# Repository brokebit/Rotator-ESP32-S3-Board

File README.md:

# Rotator-ESP32-S3-Board

# Features / Design Info
- One of the ESP32 serial ports exposes a GS-232 interface for motor control commands for connecting to a PC interfacing with rotctld from the Hamlib suite
- GPS Time Sync using NEMA GPS Module over RS232
- Serial interface for Nextion Display
- Designed for Clearpath servo motors from https://teknic.com/
- Interface for 6 Hardware Debounced buttons for manual direction control, homing and moon tracking 
- Uses pulse encoder data from the Clearpath motors for position feedback
- Power input is +10v - +25v DC
- Motors are powered by seperate power source 
- Voltage select headers to select either 3.3v or 5v logic for RS232 interfaces (GPS, LCD)
- 6 Layer Board

# Build Pics

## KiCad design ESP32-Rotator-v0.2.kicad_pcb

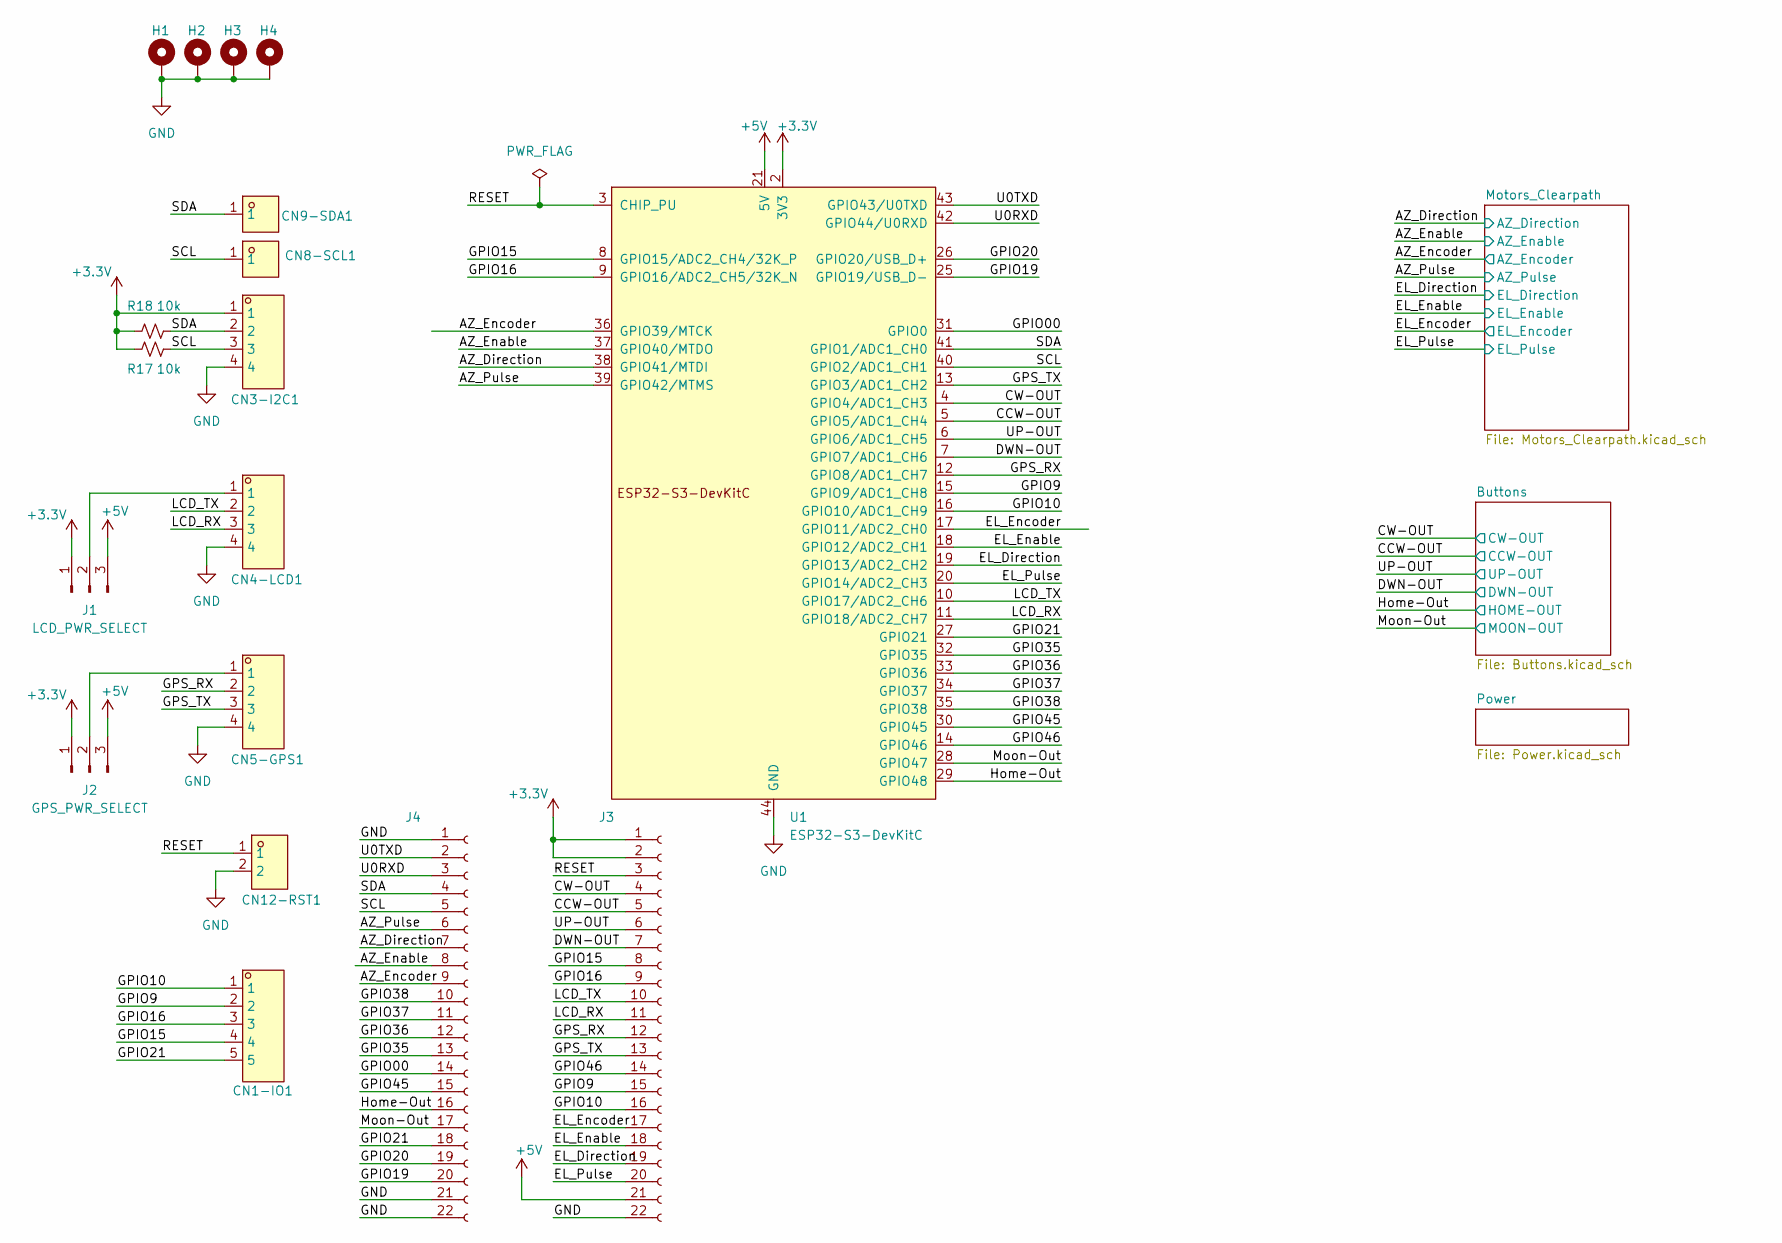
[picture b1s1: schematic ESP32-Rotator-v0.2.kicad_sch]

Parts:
CN1-IO1: WJ15EDGVC-3.81-5P; CONN-TH_WJ15EDGVC-3.81-5P; LCSC Part C8391
CN3-I2C1, CN4-LCD1, CN5-GPS1: WJ15EDGVC-3.81-4P; CONN-TH_4P-P3.81_WJ2EDGVC-3.81-4P; LCSC Part C8410
CN8-SCL1, CN9-SDA1: RH-5019; TESTPOINT-SMD_L3.8-W2.0_RH-5019; LCSC Part C5199800
CN12-RST1: KF2EDGV-3.81-2P; CONN-TH_2P-P3.81_KF2EDGV-3.81-2P; LCSC Part C441332
H1, H2, H3, H4: MountingHole_Pad; MountingHole_3.2mm_M3_Pad
J1: LCD_PWR_SELECT; PinHeader_1x03_P2.54mm_Vertical
J2: GPS_PWR_SELECT; PinHeader_1x03_P2.54mm_Vertical
J3, J4: Conn_01x22_Socket; PinSocket_1x22_P2.54mm_Vertical
R17, R18: 10k; R_0805_2012Metric
U1: ESP32-S3-DevKitC

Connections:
+3.3V: CN3-I2C1.1, J1.1, J2.1, J3.1, J3.2, R17.1, R18.1, U1.1 (3V3), U1.2 (3V3); also elsewhere on the board
+5V: J1.3, J2.3, J3.21, U1.21 (5V); also elsewhere on the board
/AZ_Direction: J4.7, U1.38 (GPIO41/MTDI); also elsewhere on the board
/AZ_Enable: J4.8, U1.37 (GPIO40/MTDO); also elsewhere on the board
/AZ_Encoder: J4.9, U1.36 (GPIO39/MTCK); also elsewhere on the board
/AZ_Pulse: J4.6, U1.39 (GPIO42/MTMS); also elsewhere on the board
/CCW-OUT: J3.5, U1.5 (GPIO5/ADC1_CH4); also elsewhere on the board
/CW-OUT: J3.4, U1.4 (GPIO4/ADC1_CH3); also elsewhere on the board
/DWN-OUT: J3.7, U1.7 (GPIO7/ADC1_CH6); also elsewhere on the board
/EL_Direction: J3.19, U1.19 (GPIO13/ADC2_CH2); also elsewhere on the board
/EL_Enable: J3.18, U1.18 (GPIO12/ADC2_CH1); also elsewhere on the board
/EL_Encoder: J3.17, U1.17 (GPIO11/ADC2_CH0); also elsewhere on the board
/EL_Pulse: J3.20, U1.20 (GPIO14/ADC2_CH3); also elsewhere on the board
/GPIO00: J4.14, U1.31 (GPIO0)
/GPIO9: CN1-IO1.2, J3.15, U1.15 (GPIO9/ADC1_CH8)
/GPIO10: CN1-IO1.1, J3.16, U1.16 (GPIO10/ADC1_CH9)
/GPIO15: CN1-IO1.4, J3.8, U1.8 (GPIO15/ADC2_CH4/32K_P)
/GPIO16: CN1-IO1.3, J3.9, U1.9 (GPIO16/ADC2_CH5/32K_N)
/GPIO19: J4.20, U1.25 (GPIO19/USB_D-)
/GPIO20: J4.19, U1.26 (GPIO20/USB_D+)
/GPIO21: CN1-IO1.5, J4.18, U1.27 (GPIO21)
/GPIO35: J4.13, U1.32 (GPIO35)
/GPIO36: J4.12, U1.33 (GPIO36)
/GPIO37: J4.11, U1.34 (GPIO37)
/GPIO38: J4.10, U1.35 (GPIO38)
/GPIO45: J4.15, U1.30 (GPIO45)
/GPIO46: J3.14, U1.14 (GPIO46)
/GPS_RX: CN5-GPS1.2, J3.12, U1.12 (GPIO8/ADC1_CH7)
/GPS_TX: CN5-GPS1.3, J3.13, U1.13 (GPIO3/ADC1_CH2)
/Home-Out: J4.16, U1.29 (GPIO48); also elsewhere on the board
/LCD_RX: CN4-LCD1.3, J3.11, U1.11 (GPIO18/ADC2_CH7)
/LCD_TX: CN4-LCD1.2, J3.10, U1.10 (GPIO17/ADC2_CH6)
/Moon-Out: J4.17, U1.28 (GPIO47); also elsewhere on the board
/RESET: CN12-RST1.1, J3.3, U1.3 (CHIP_PU)
/SCL: CN3-I2C1.3, CN8-SCL1.1, J4.5, R17.2, U1.40 (GPIO2/ADC1_CH1)
/SDA: CN3-I2C1.2, CN9-SDA1.1, J4.4, R18.2, U1.41 (GPIO1/ADC1_CH0)
/U0RXD: J4.3, U1.42 (GPIO44/U0RXD)
/U0TXD: J4.2, U1.43 (GPIO43/U0TXD)
/UP-OUT: J3.6, U1.6 (GPIO6/ADC1_CH5); also elsewhere on the board
GND: CN3-I2C1.4, CN4-LCD1.4, CN5-GPS1.4, CN12-RST1.2, H1.1, H2.1, H3.1, H4.1, J3.22, J4.1, J4.21, J4.22, U1.22 (GND), U1.23 (GND), U1.24 (GND), U1.44 (GND); also elsewhere on the board
unnamed: CN4-LCD1.1, J1.2
unnamed: CN5-GPS1.1, J2.2

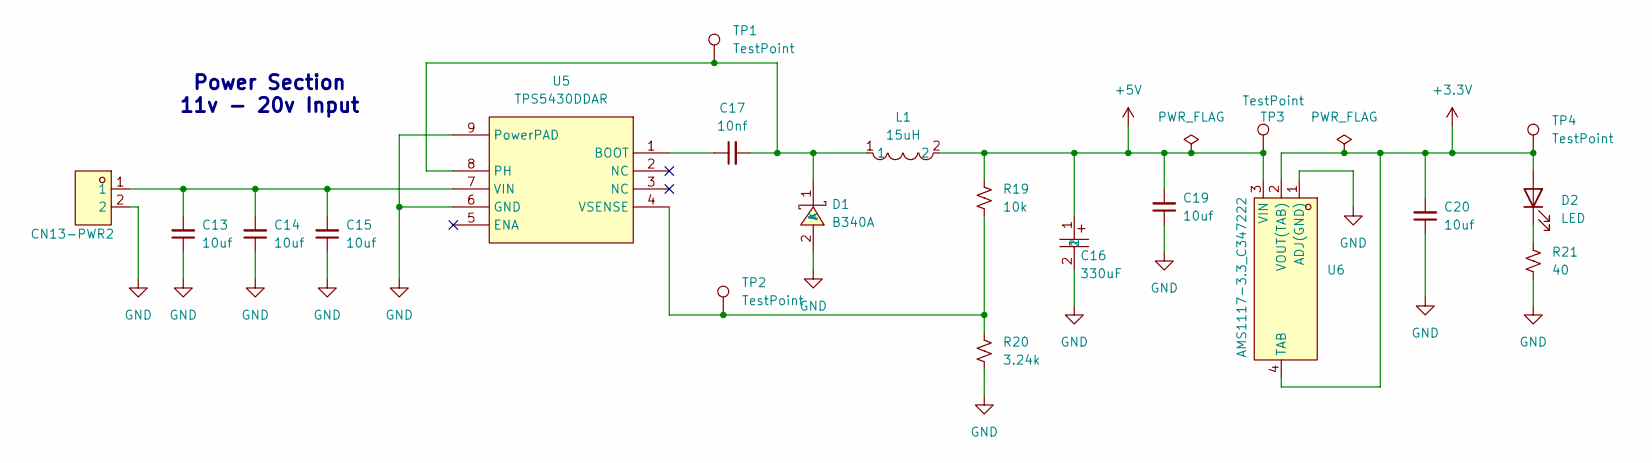
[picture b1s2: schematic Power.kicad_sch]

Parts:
C13, C14, C15, C19, C20: 10uf; C_0603_1608Metric
C16: 330uF; CAP-SMD_L7.3-W4.3-R-RD; LCSC Part C79112
C17: 10nf; C_0603_1608Metric
CN13-PWR2: KF2EDGV-3.81-2P; CONN-TH_2P-P3.81_KF2EDGV-3.81-2P; LCSC Part C441332
D1: B340A; SMA_L4.3-W2.6-LS5.1-RD; LCSC Part C64982
D2: LED; LED_0805_2012Metric; LCSC Part C84260
L1: 15uH; IND-SMD_L12.5-W12.5_RLF12545T; LCSC Part C40000
R19: 10k; R_0603_1608Metric
R20: 3.24k; R_0603_1608Metric
R21: 40; R_0805_2012Metric; LCSC Part C2930194
TP1, TP2, TP3, TP4: TestPoint; TestPoint_Pad_1.5x1.5mm
U5: TPS5430DDAR; ESOP-8_L4.9-W3.9-P1.27-LS6.0-TL-EP; LCSC Part C9864
U6: AMS1117-3.3_C347222; SOT-223-4_L6.5-W3.5-P2.30-LS7.0-BR; LCSC Part C347222

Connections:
+3.3V: C20.2, D2.2 (A), TP4.1, U6.2 (VOUT(TAB)), U6.4 (TAB); also elsewhere on the board
+5V: C16.1, C19.2, L1.2, R19.1, TP3.1, U6.3 (VIN); also elsewhere on the board
GND: C13.1, C14.1, C15.1, C16.2, C19.1, C20.1, CN13-PWR2.2, D1.2 (A), R20.2, R21.2, U5.6 (GND), U5.9 (PowerPAD), U6.1 (ADJ(GND)); also elsewhere on the board
unnamed: C17.2, D1.1 (K), L1.1, TP1.1, U5.8 (PH)
unnamed: D2.1 (K), R21.1
unnamed: C17.1, U5.1 (BOOT)
unnamed: C13.2, C14.2, C15.2, CN13-PWR2.1, U5.7 (VIN)
unnamed: R19.2, R20.1, TP2.1, U5.4 (VSENSE)

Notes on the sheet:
Power Section 11v - 20v Input

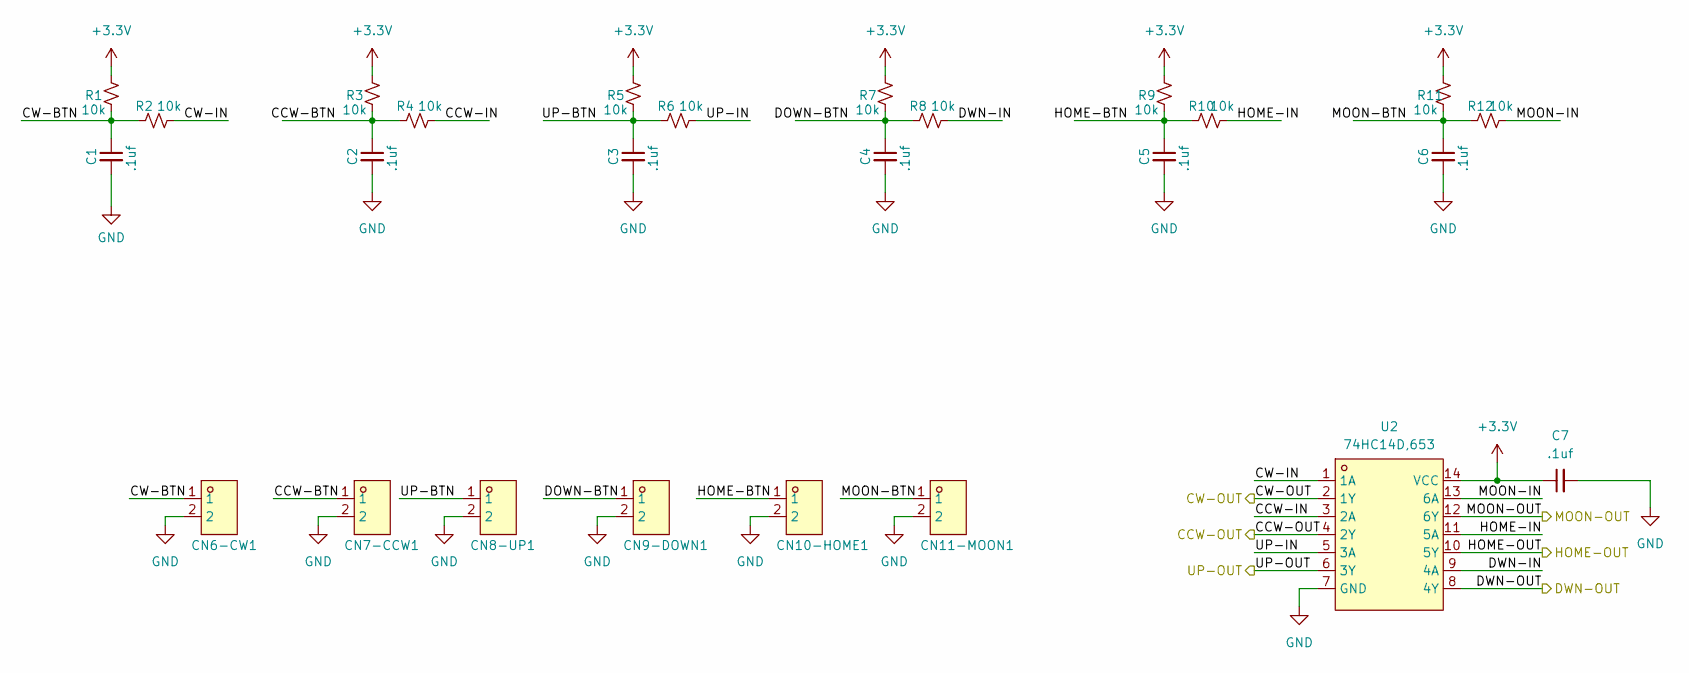
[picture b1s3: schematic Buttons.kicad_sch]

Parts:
C1, C2, C3, C4, C5, C6, C7: .1uf; C_0805_2012Metric
CN6-CW1, CN7-CCW1, CN8-UP1, CN9-DOWN1, CN10-HOME1, CN11-MOON1: KF2EDGV-3.81-2P; CONN-TH_2P-P3.81_KF2EDGV-3.81-2P; LCSC Part C441332
R1, R2, R3, R4, R5, R6, R7, R8, R9, R10, R11, R12: 10k; R_0805_2012Metric
U2: 74HC14D,653; SOIC-14_L8.7-W3.9-P1.27-LS6.0-BL; LCSC Part C5605

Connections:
+3.3V: C7.1, R1.1, R3.1, R5.1, R7.1, R9.1, R11.1, U2.14 (VCC); also elsewhere on the board
/Buttons/CCW-BTN: C2.1, CN7-CCW1.1, R3.2, R4.2
/Buttons/CCW-IN: R4.1, U2.3 (2A)
/Buttons/CW-BTN: C1.1, CN6-CW1.1, R1.2, R2.2
/Buttons/CW-IN: R2.1, U2.1 (1A)
/Buttons/DOWN-BTN: C4.1, CN9-DOWN1.1, R7.2, R8.2
/Buttons/DWN-IN: R8.1, U2.9 (4A)
/Buttons/HOME-BTN: C5.1, CN10-HOME1.1, R9.2, R10.2
/Buttons/HOME-IN: R10.1, U2.11 (5A)
/Buttons/MOON-BTN: C6.1, CN11-MOON1.1, R11.2, R12.2
/Buttons/MOON-IN: R12.1, U2.13 (6A)
/Buttons/UP-BTN: C3.1, CN8-UP1.1, R5.2, R6.2
/Buttons/UP-IN: R6.1, U2.5 (3A)
/CCW-OUT: U2.4 (2Y); also elsewhere on the board
/CW-OUT: U2.2 (1Y); also elsewhere on the board
/DWN-OUT: U2.8 (4Y); also elsewhere on the board
/Home-Out: U2.10 (5Y); also elsewhere on the board
/Moon-Out: U2.12 (6Y); also elsewhere on the board
/UP-OUT: U2.6 (3Y); also elsewhere on the board
GND: C1.2, C2.2, C3.2, C4.2, C5.2, C6.2, C7.2, CN6-CW1.2, CN7-CCW1.2, CN8-UP1.2, CN9-DOWN1.2, CN10-HOME1.2, CN11-MOON1.2, U2.7 (GND); also elsewhere on the board

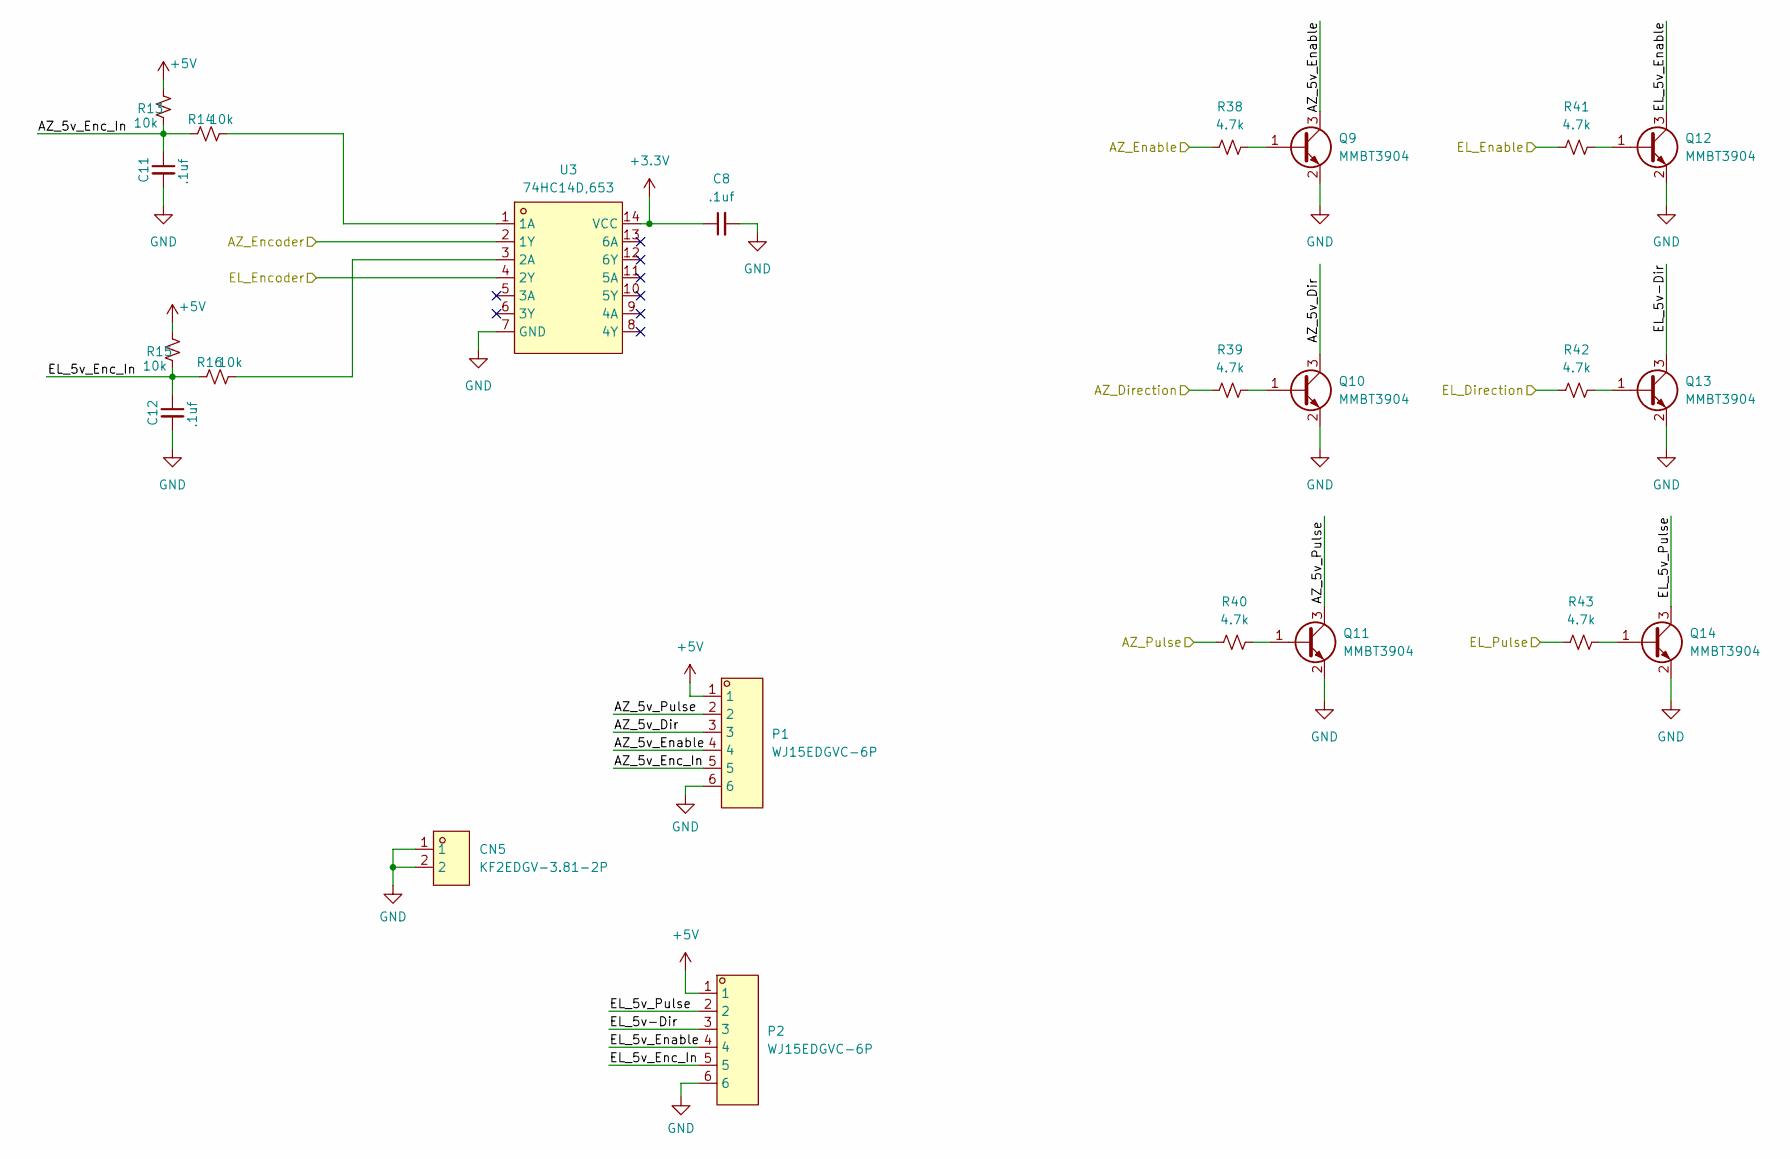
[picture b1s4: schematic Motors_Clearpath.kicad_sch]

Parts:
C8, C11, C12: .1uf; C_0805_2012Metric
CN5: KF2EDGV-3.81-2P; CONN-TH_2P-P3.81_KF2EDGV-3.81-2P; LCSC Part C441332
P1, P2: WJ15EDGVC-6P; CONN-TH_6P_WJ15EDGVC-3.81-6P; LCSC Part C8415
Q9, Q10, Q11, Q12, Q13, Q14: MMBT3904; SOT-23
R13, R14, R15, R16: 10k; R_0805_2012Metric
R38, R39, R40, R41, R42, R43: 4.7k; R_0805_2012Metric
U3: 74HC14D,653; SOIC-14_L8.7-W3.9-P1.27-LS6.0-BL; LCSC Part C5605

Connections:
+3.3V: C8.1, U3.14 (VCC); also elsewhere on the board
+5V: P1.1, P2.1, R13.1, R15.1; also elsewhere on the board
/AZ_Direction: R39.1; also elsewhere on the board
/AZ_Enable: R38.1; also elsewhere on the board
/AZ_Encoder: U3.2 (1Y); also elsewhere on the board
/AZ_Pulse: R40.1; also elsewhere on the board
/EL_Direction: R42.1; also elsewhere on the board
/EL_Enable: R41.1; also elsewhere on the board
/EL_Encoder: U3.4 (2Y); also elsewhere on the board
/EL_Pulse: R43.1; also elsewhere on the board
/Motors_Clearpath/AZ_5v_Dir: P1.3, Q10.3 (C)
/Motors_Clearpath/AZ_5v_Enable: P1.4, Q9.3 (C)
/Motors_Clearpath/AZ_5v_Enc_In: C11.1, P1.5, R13.2, R14.2
/Motors_Clearpath/AZ_5v_Pulse: P1.2, Q11.3 (C)
/Motors_Clearpath/EL_5v-Dir: P2.3, Q13.3 (C)
/Motors_Clearpath/EL_5v_Enable: P2.4, Q12.3 (C)
/Motors_Clearpath/EL_5v_Enc_In: C12.1, P2.5, R15.2, R16.2
/Motors_Clearpath/EL_5v_Pulse: P2.2, Q14.3 (C)
GND: C8.2, C11.2, C12.2, CN5.1, CN5.2, P1.6, P2.6, Q9.2 (E), Q10.2 (E), Q11.2 (E), Q12.2 (E), Q13.2 (E), Q14.2 (E), U3.7 (GND); also elsewhere on the board
unnamed: Q9.1 (B), R38.2
unnamed: Q10.1 (B), R39.2
unnamed: Q11.1 (B), R40.2
unnamed: Q12.1 (B), R41.2
unnamed: Q13.1 (B), R42.2
unnamed: Q14.1 (B), R43.2
unnamed: R14.1, U3.1 (1A)
unnamed: R16.1, U3.3 (2A)

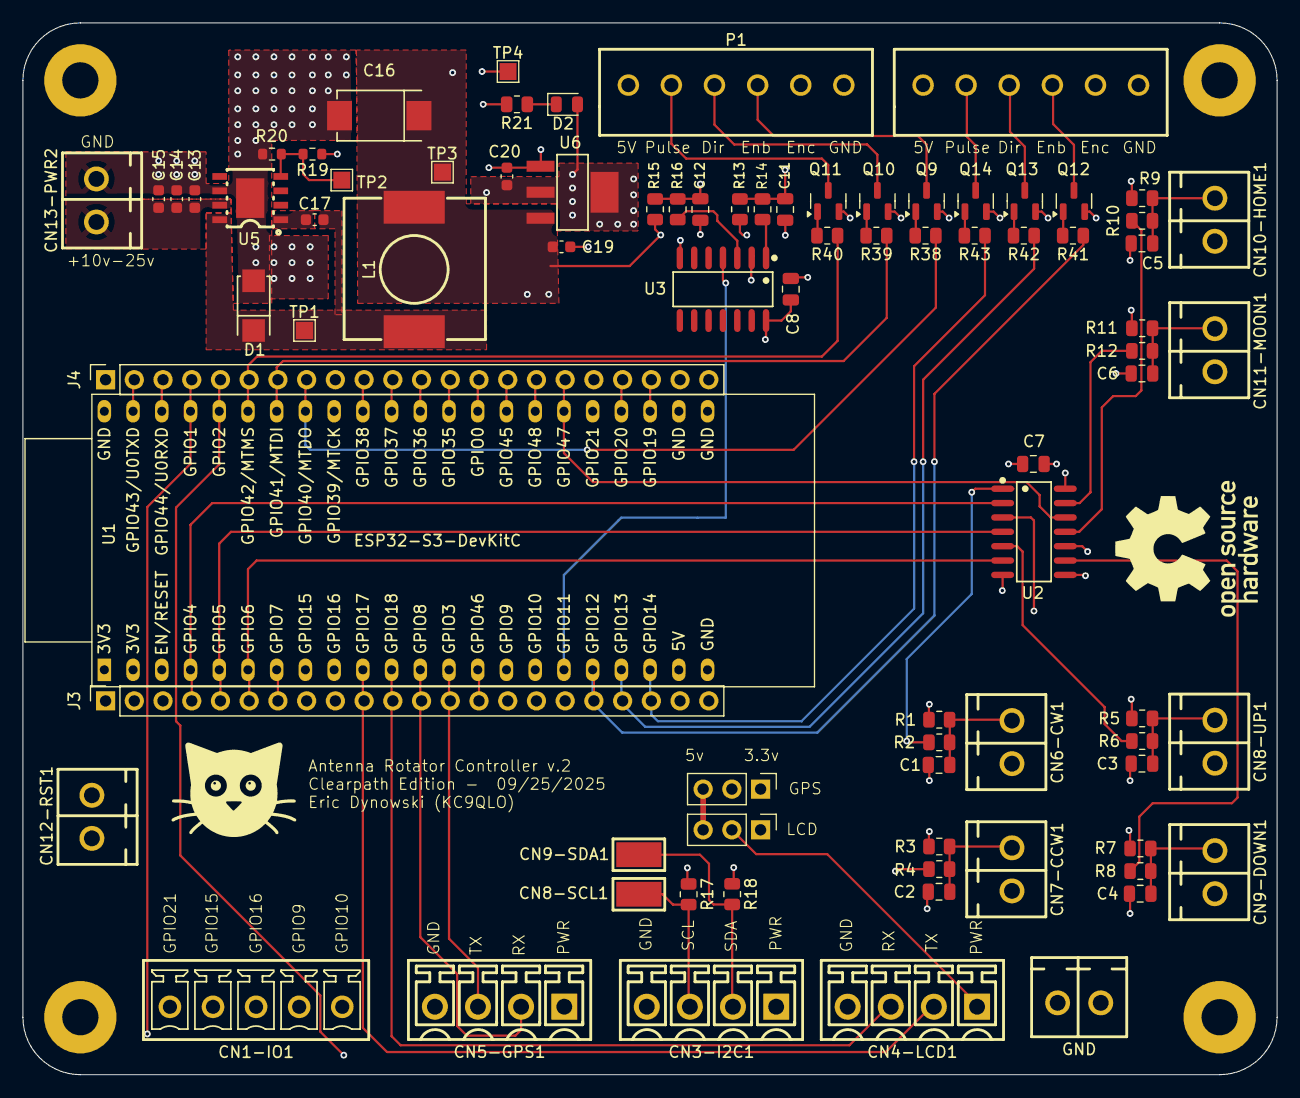
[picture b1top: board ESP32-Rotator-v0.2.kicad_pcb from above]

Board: 6 copper layers, 110.9 x 93.0 mm, 87 parts (0 on the bottom side), 75 nets.

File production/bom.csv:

Designator,Footprint,Quantity,Value,LCSC Part #
"C1, C11, C12, C2, C3, C4, C5, C6, C7, C8",0805,10,.1uf,
"C13, C14, C15, C19, C20",0603,5,10uf,
C16,CAP-SMD_L7.3-W4.3-R-RD,1,330uF,C79112
C17,0603,1,10nf,
CN1-IO1,CONN-TH_WJ15EDGVC-3.81-5P,1,WJ15EDGVC-3.81-5P,C8391
"CN10-HOME1, CN11-MOON1, CN12-RST1, CN13-PWR2, CN5, CN6-CW1, CN7-CCW1, CN8-UP1, CN9-DOWN1",CONN-TH_2P-P3.81_KF2EDGV-3.81-2P,9,KF2EDGV-3.81-2P,C441332
"CN3-I2C1, CN4-LCD1, CN5-GPS1",CONN-TH_4P-P3.81_WJ2EDGVC-3.81-4P,3,WJ15EDGVC-3.81-4P,C8410
"CN8-SCL1, CN9-SDA1",TESTPOINT-SMD_L3.8-W2.0_RH-5019,2,RH-5019,C5199800
D1,SMA_L4.3-W2.6-LS5.1-RD,1,B340A,C64982
D2,0805,1,LED,C84260
J1,PinHeader_1x03_P2.54mm_Vertical,1,LCD_PWR_SELECT,
J2,PinHeader_1x03_P2.54mm_Vertical,1,GPS_PWR_SELECT,
"J3, J4",PinSocket_1x22_P2.54mm_Vertical,2,Conn_01x22_Socket,
L1,IND-SMD_L12.5-W12.5_RLF12545T,1,15uH,C40000
"P1, P2",CONN-TH_6P_WJ15EDGVC-3.81-6P,2,WJ15EDGVC-6P,C8415
"Q10, Q11, Q12, Q13, Q14, Q9",SOT-23,6,MMBT3904,
"R1, R10, R11, R12, R13, R14, R15, R16, R17, R18, R2, R3, R4, R5, R6, R7, R8, R9",0805,18,10k,
R19,0603,1,10k,
R20,0603,1,3.24k,
R21,0805,1,40,C2930194
"R38, R39, R40, R41, R42, R43",0805,6,4.7k,
"TP1, TP2, TP3, TP4",TestPoint_Pad_1.5x1.5mm,4,TestPoint,
U1,ESP32-S3-DevKitC,1,ESP32-S3-DevKitC,
"U2, U3",SOIC-14_L8.7-W3.9-P1.27-LS6.0-BL,2,"74HC14D,653",C5605
U5,ESOP-8_L4.9-W3.9-P1.27-LS6.0-TL-EP,1,TPS5430DDAR,C9864
U6,SOT-223-4_L6.5-W3.5-P2.30-LS7.0-BR,1,AMS1117-3.3_C347222,C347222

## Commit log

2026-02-11 Initial commit of board design
2026-02-11 Add Rendering
2026-02-11 Add rendering and git ignore
2026-02-11 Add some pictures
